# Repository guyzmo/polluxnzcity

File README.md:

Pollux'NZ City Project
======================

The pollux'NZ City project aims at creating a network of autonomous wireless network
of sensors that uploads the measures on any data silos on Internet.

This repository contains the source code of the first prototype of the project, that
has been deployed  in south of France, with the participation of INRIA Sofia Antipolis,
for a first test run.

Description
===========

The projects is made of two modules:
 * the 'autonomous measuring module', that is made of
   * an arduino with a zigbee radio module ;
   * a battery pack that powers the system ;
   * a solar panel that charges the battery ;
   * an i2c network of sensors.
 * the 'gateway module', that is made of
   * a beaglebone with a zigbee radio module

How it works ?
==============

First, after pluging it in, the user configures the gateway module for his sensor 
network and the interval time between two measures. Then he places the autonomous
sensor module to the best sunlight exposure so the autonomous measuring module can
keep the battery filled up.

The gateway will wait for the given interval time, and waken up the measuring module.
It will then order the measuring module to run the fan, so a free air sample is taken
into the box and run in sequence each sensor to get the measured value. Once all the
sensors have been interrogated, it will tell the measuring module to shut itself down.
Finally, all the measures are given to the enabled plugins that will push the data to
every configured data silo.

Project details
===============

Structure of the project
------------------------

 * Directories

<pre>
PolluxNZCity
    |-- PolluxConfig ............. Contains the configuration plugin (in python)
    |   |-- debian ............... Helper files for package generation
    |   |-- pollux ............... Python module
    |-- PolluxGateway ............ Main program that interfaces with the measuring modules
    |   |-- conf ................. Configuration files that are to be deployed in /etc
    |   |-- extensions ........... Python plugins for uploading data to data silos
    |   |-- include .............. Headers
    |   |-- src .................. Sources
    |   `-- tests ................ Tools that helps testing
    |-- PolluxWakeupduino ........ Main firmware code for the arduino in the measuring module
    |-- PolluxSensorBoard ........ Firmware code for the fan, temperature and noise board
    |-- PolluxSensorDust ......... Firmware code for the dust board
    |-- PolluxSensorSensoric ..... Firmware code for the electrochemical sensoric sensors board
    |-- PolluxSensorTemp ......... Firmware code for the external temperature sensor board
    `-- PolluxContribIpks ........ Helper scripts to build binary packages (for angstrom)
</pre>

 * Branches
   * inria_branch: contains the source code deployed for the INRIA test run
   * i2c_refactoring: non-tested base for a full refactoring of the i2c network

 * Other

In PolluxContribIpks, the package.sh script will run a build and generate the packages
– PolluxConfig and PolluxGateway – that are embedded on the beaglebone. That generator
is now deprecated, the recipes for generating those packages working and being accessible
for the angstrom build system.

Description of the main modules
-------------------------------

* _PolluxConfig_: this module is a web application based on the `bottle.py` module that
  exposes RESTful pathes to the web interface that exposes them using `bootstrap.js`.
  The most important parts are in the `pollux_config` module that contains all the exposed
  routes.
* _PolluxGateway_: this module is the main program that parses the configuration, runs 
  the radio, interrogates every sensor on the distant modules and sends the results
  through every datastore module.
* _PolluxWakeUpduino_: this firmware is the code executed by the embedded arduino that
  is only a gateway between XBee and the i2c network.

The _PolluxGateway_ module has documentation embedded you can generate using `doxygen`,
or by running `make doc` in the directory.

Build and Install
-----------------

* _PolluxConfig_

<pre>
 % cd PolluxConfig
 % python bootstrap.py
 % bin/buildout
 % bin/pollux_config_paster
</pre>

* _PolluxGateway_

first you will need to install the arm-gcc for crosscompilation, or run it directly
on a beaglebone, using native gcc.

<pre>
 % make
 % make doc
 % pollux\_gateway -h
</pre>

for a more verbose version of the software, you can run `make verbose`, that will
create a `pollux\_gateway\_verbose` executable.

Caveats
=======

* The I2C model has been mis-designed. 

We have implemented the i2c stack of the whole project following the way the i2c model
has been implemented in the Arduino and ATTiny wire library suggested ; so we followed
a function calling alike protocol.

But we rapidely found out that this kind of implementation is flawed for our use of 
i2c, as it is not flexible enough and not compatible with most of the i2c modules of
the market. So there's a unfinished implementation of the new i2c handling in the
`i2c_refactoring` branch. That has been not tested at all, and not all the sensors'
firmware has been switched to it.

* The _PolluxGateway_ modules deserves better verbosity

First, instead of compiling two different targets, it should have the common `-v`
switch that makes the executable output more messages. But the verbosity shall also
have levels, so the output is not flooded by the messages.

* The _PolluxGateway_ module shall not configure the MUX values for the xbee cape

We have implemented our first versions of the XBee Cape without the helper EEPROM
that helps the cape autoconfigure the MUX values of the beaglebone. With the new
version of the cape, all the code that configures the MUX settings shall be dropped.
This will finally makes the module work only in userland, and not need to start as
root and drop its privileges once the MUX settings are set.

* The _PolluxGateway_ module and _PolluxWakeUpduino_ firmware shall configure all the zigbee settings

We rely on the manual setting of the XBee modules, to match them up and to configure
their pin ports. That operation is cumbersome, does not work all the time, and needs
to use the X-CTU application under windows.

TODO
====

* finish the refactoring of the i2c stacks
* add more verbosity to the _PolluxGateway_ module
* remove the MUX configuration at _PolluxGateway_ start
* add configuration of the XBee radios in the _PolluxGateway_ module and
  _PolluxWakeUpduino_ firmware.

Copyright
=========

(c)2011-2013 Lucas Fernandez and Bernard Pratz, CKAB, hackable:Devices

 * http://polluxnzcity.org/
 * http://ckab.com/polluxnz-city/
 * http://hackable-devices.org/projects/project/polluxnzcity/

All our original work is licensed under the GNU GPL version 3
and all our schematics are under the Creative Commons v3.0 Attribution Share-Alike.

Here are the Libraries we use in our projects, and their respective copyrights notice

Arduino libraries:
 * Statistics by Rob Tillaart and Gil Ross, in the Public Domain 
 * usiTwiSlave, by Donald R. Blake, Jochen Toppe and Ben Galvin under GPL v2
 * circular buffer based on Akash Nath, in the Public Domain
 * Arduino, by the Arduino team, under the GPL v2

For the python web interface:
 * bottle.py under the MIT License
 * bootstrap.js under the Apache License v2.0.
 * deansi library by David Garcia Garzon, under the AGPLv3

All components symbols in the schematics are from Eagle's libraries, under Creative
Commons v3.0 Share-Alike.

License
=======

This program is free software: you can redistribute it and/or modify
it under the terms of the GNU General Public License as published by
the Free Software Foundation, either version 3 of the License, or
(at your option) any later version.

This program is distributed in the hope that it will be useful,
but WITHOUT ANY WARRANTY; without even the implied warranty of
MERCHANTABILITY or FITNESS FOR A PARTICULAR PURPOSE.  See the
GNU General Public License for more details.

You should have received a copy of the GNU General Public License
along with this program.  If not, see <http://www.gnu.org/licenses/>.

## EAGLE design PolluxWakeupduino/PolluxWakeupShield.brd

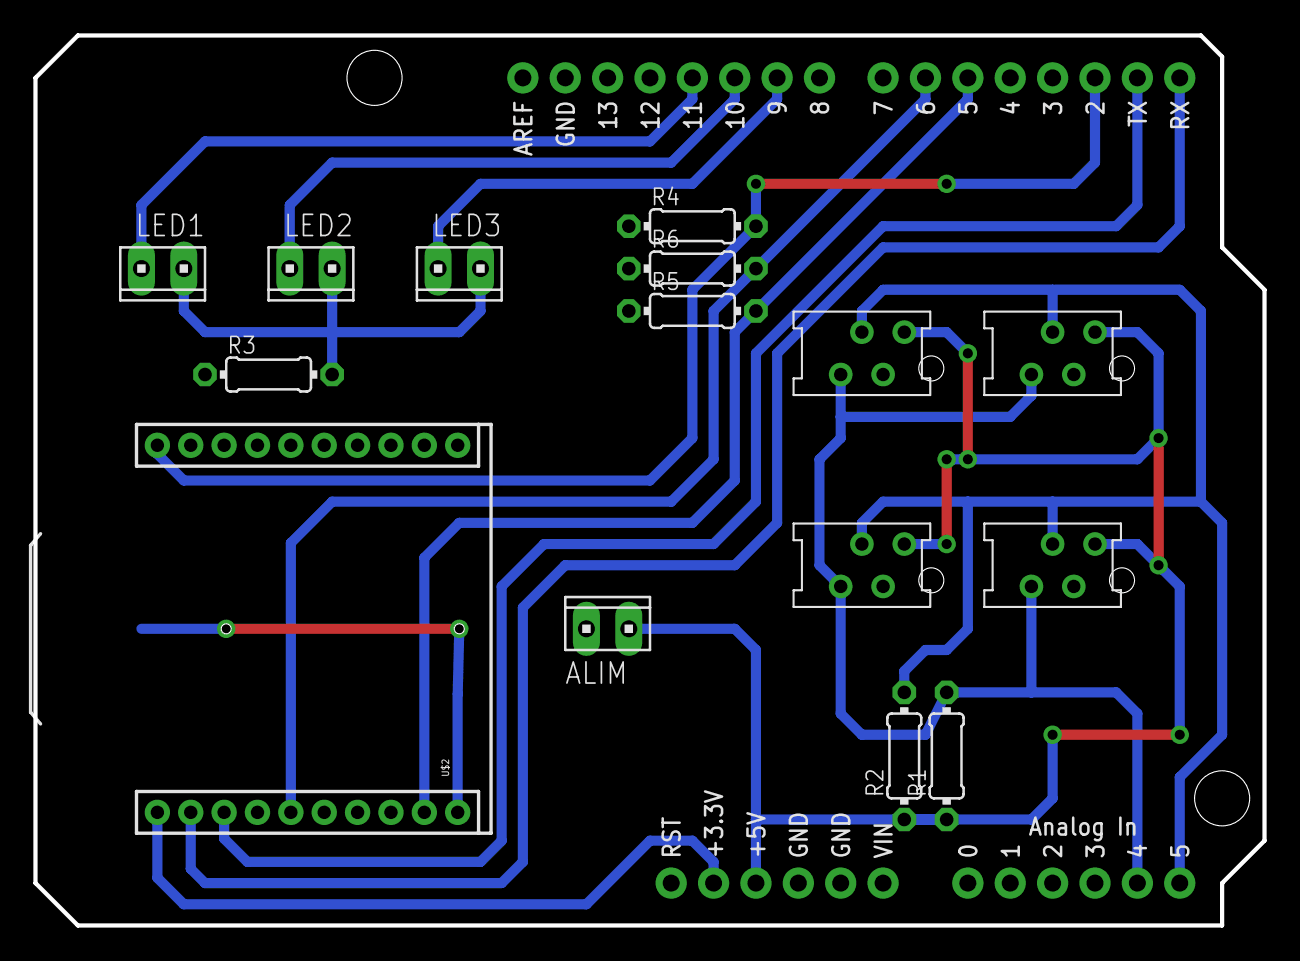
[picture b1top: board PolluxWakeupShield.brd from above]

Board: 2 copper layers, 73.7 x 53.3 mm, 16 parts (0 on the bottom side), 14 nets.

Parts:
ALIM: 10X02MTA
I2C-0, I2C-1, I2C-2, I2C-3: MMATCH-4-PTH; AMP-215079-4
LED1, LED2, LED3: 10X02MTA
R1, R2, R4, R5, R6: 10k; 0204/7
R3: 50; 0204/7
U1: ARDUINO_SHIELD; DUEMILANOVE_SHIELD
U$2: XBEE-1B2; XBEE-SILK

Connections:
3.3V: U1.3.3V, U$2.1
5V: ALIM.1, I2C-0.1, I2C-1.1, I2C-2.1, I2C-3.1, R1.1, R2.1, U1.5V
GND: ALIM.2, I2C-0.2, I2C-1.2, I2C-2.2, I2C-3.2, R3.1, R4.1, R5.1, R6.1, U1.GND@0, U1.GND@1, U1.GND@2, U$2.10
unnamed: LED1.2, LED2.2, LED3.2, R3.2
unnamed: LED3.1, U1.D9
unnamed: LED2.1, U1.D10
unnamed: LED1.1, U1.D11
RESET: R6.2, U1.D6, U$2.5
RX: U1.RX, U$2.2
SCL: I2C-0.3, I2C-1.3, I2C-2.3, I2C-3.3, R2.2, U1.A5
SDA: I2C-0.4, I2C-1.4, I2C-2.4, I2C-3.4, R1.2, U1.A4
SLEEP: R5.2, U1.D5, U$2.9
TX: U1.TX, U$2.3
WAKEUP: R4.2, U1.D2, U$2.20

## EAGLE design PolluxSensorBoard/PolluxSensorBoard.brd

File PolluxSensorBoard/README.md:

Sensor board for final fing pollux.

This sensor board include :
* temperature
* SPL
* Dust PM10

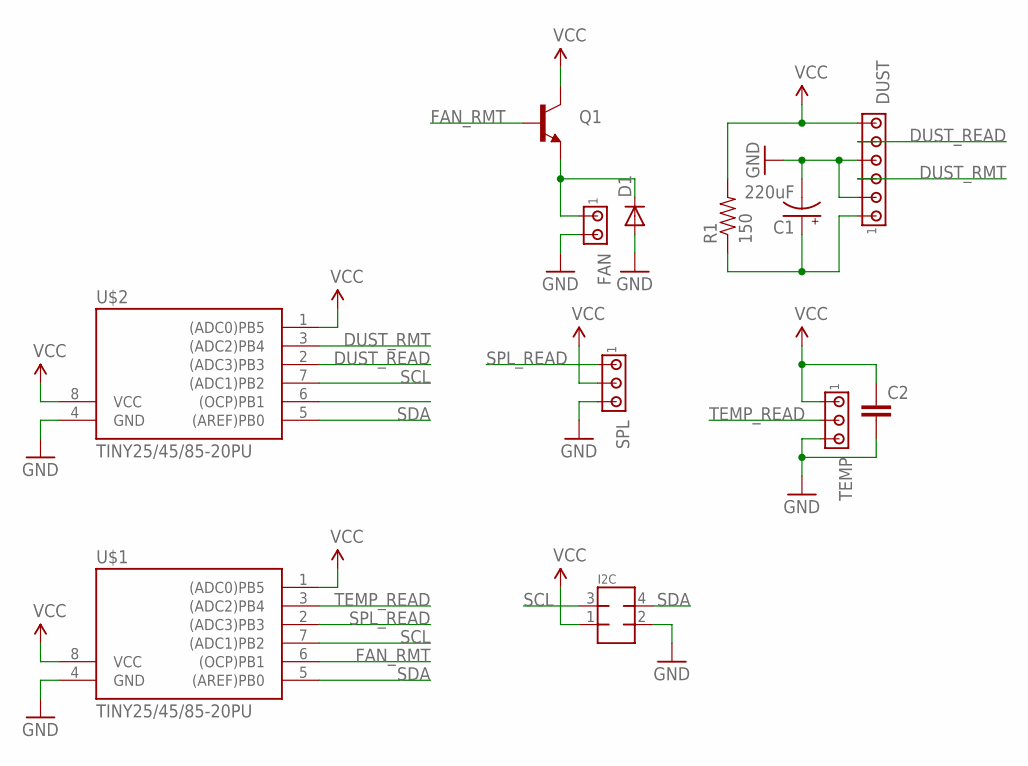
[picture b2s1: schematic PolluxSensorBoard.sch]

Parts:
C1: 220uF; CPOL-RADIAL-1000UF-25V
C2: CAPPTH1; CAP-PTH-5MM
D1: DIODEPTH; DIODE-1N4001
DUST: MTA06-100; 10X06MTA
FAN: MTA02-100; 10X02MTA
I2C: MMATCH-8-PTH; AMP-215079-8
Q1: TRANSISTOR_NPNTO-92-AMMO; TO-92-AMMO
R1: 150; AXIAL-0.4
SPL: MTA03-100; 10X03MTA
TEMP: MTA03-100; 10X03MTA
U$1, U$2: TINY25/45/85-20PU; DIL08

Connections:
DUST_READ: DUST.2 (5), U$2.2 ((ADC3)PB3)
DUST_RMT: DUST.4 (3), U$2.3 ((ADC2)PB4)
FAN_RMT: Q1.2 (B), U$1.6 ((OCP)PB1)
GND: C1.2 (-), C2.2, D1.A, DUST.3 (4), DUST.5 (2), FAN.2, I2C.2, SPL.3, TEMP.3, U$1.4 (GND), U$2.4 (GND)
unnamed: D1.C, FAN.1, Q1.1 (E)
unnamed: C1.1 (+), DUST.6 (1), R1.P$1 (1)
SCL: I2C.3, U$1.7 ((ADC1)PB2), U$2.7 ((ADC1)PB2)
SDA: I2C.4, U$1.5 ((AREF)PB0), U$2.5 ((AREF)PB0)
SPL_READ: SPL.1, U$1.2 ((ADC3)PB3)
TEMP_READ: TEMP.2, U$1.3 ((ADC2)PB4)
VCC: C2.1, DUST.1 (6), I2C.1, Q1.3 (C), R1.P$2 (2), SPL.2, TEMP.1, U$1.1 ((ADC0)PB5), U$1.8 (VCC), U$2.1 ((ADC0)PB5), U$2.8 (VCC)

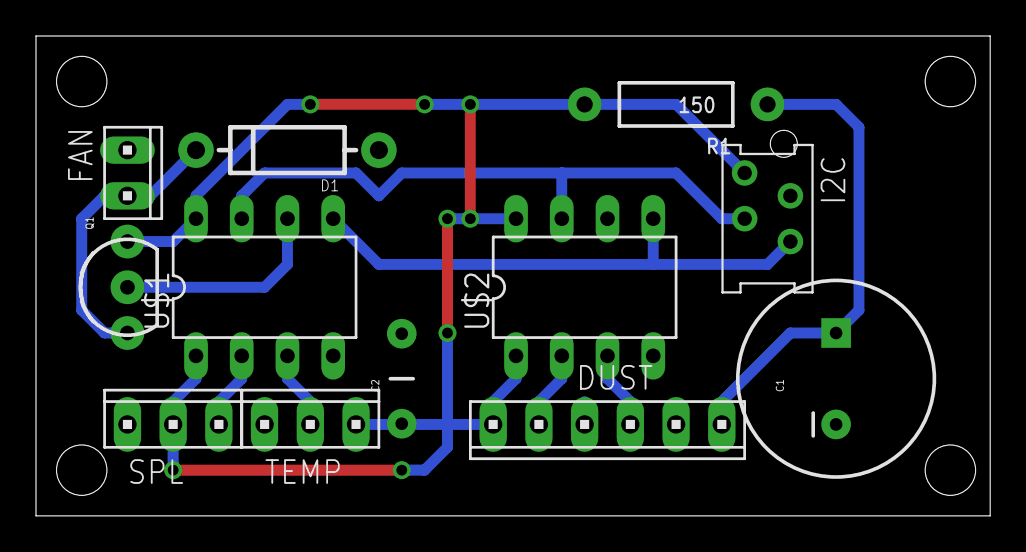
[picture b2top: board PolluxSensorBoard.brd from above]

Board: 2 copper layers, 53.0 x 26.7 mm, 12 parts (0 on the bottom side), 11 nets.

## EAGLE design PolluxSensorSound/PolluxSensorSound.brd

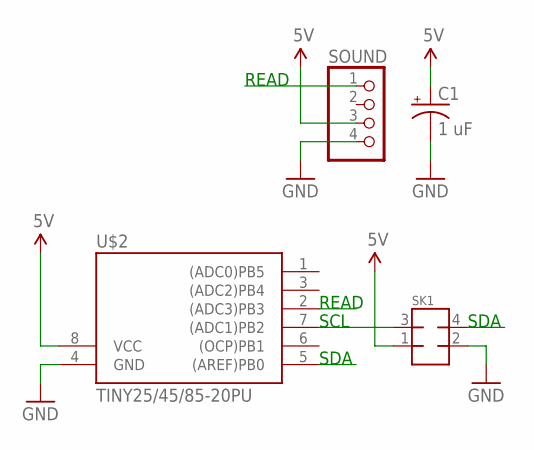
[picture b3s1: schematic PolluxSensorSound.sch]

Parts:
C1: 1 uF; CPOL-RADIAL-10UF-25V
SK1: MMATCH-8-PTH; AMP-215079-8
SOUND: PINHD-1X04_2.00; 1X04M
U$2: TINY25/45/85-20PU; DIL08

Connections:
5V: C1.1 (+), SK1.1, SOUND.3, U$2.8 (VCC)
GND: C1.2 (-), SK1.2, SOUND.4, U$2.4 (GND)
unnamed: SK1.3, U$2.7 ((ADC1)PB2)
READ: SOUND.1, U$2.2 ((ADC3)PB3)
SDA: SK1.4, U$2.5 ((AREF)PB0)

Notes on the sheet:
READ
SDA
SCL

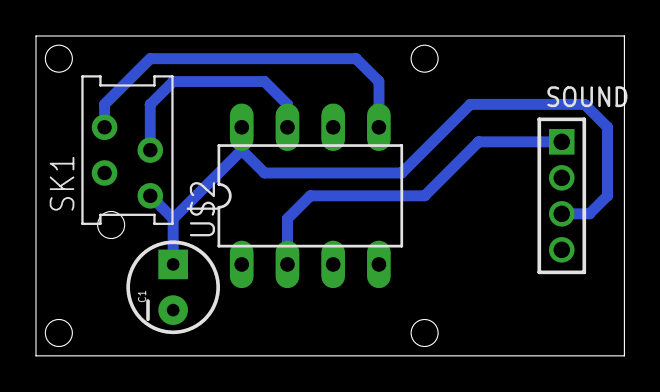
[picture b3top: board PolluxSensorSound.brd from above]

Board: 2 copper layers, 32.7 x 17.8 mm, 4 parts (0 on the bottom side), 5 nets.

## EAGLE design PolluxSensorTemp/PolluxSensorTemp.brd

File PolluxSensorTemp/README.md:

Board for dust detection for final fing pollux.

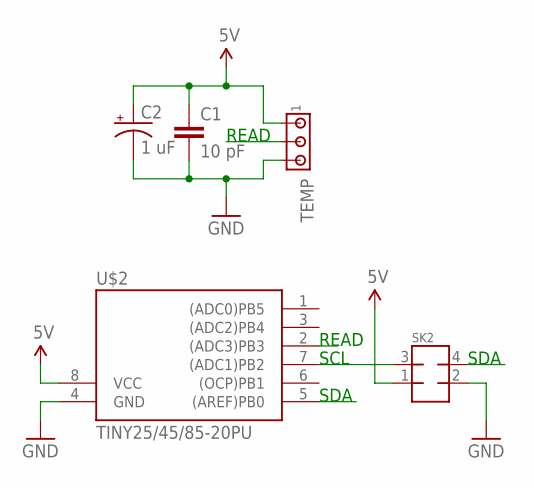
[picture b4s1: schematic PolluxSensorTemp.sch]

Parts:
C1: 10 pF; CAP-PTH-5MM
C2: 1 uF; CPOL-RADIAL-10UF-25V
SK2: MMATCH-8-PTH; AMP-215079-8
TEMP: MTA03-100; 10X03MTA
U$2: TINY25/45/85-20PU; DIL08

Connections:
5V: C1.1, C2.1 (+), SK2.1, TEMP.1, U$2.8 (VCC)
GND: C1.2, C2.2 (-), SK2.2, TEMP.3, U$2.4 (GND)
unnamed: SK2.3, U$2.7 ((ADC1)PB2)
READ: TEMP.2, U$2.2 ((ADC3)PB3)
SDA: SK2.4, U$2.5 ((AREF)PB0)

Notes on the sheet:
READ
SCL
SDA

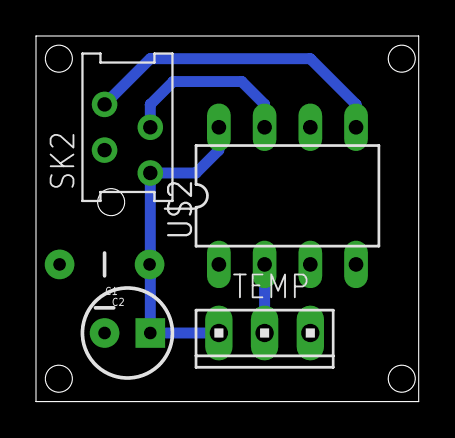
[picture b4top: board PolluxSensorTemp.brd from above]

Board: 2 copper layers, 21.3 x 20.3 mm, 5 parts (0 on the bottom side), 5 nets.

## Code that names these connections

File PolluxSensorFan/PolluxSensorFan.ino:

/*
             +-\/-+
   (RESET)  1|    |8  VCC (2.7-5.5V)
   NA ADC3  2|    |7  I2C   SCK -> Uno A5
       FAN  3|    |6  (PB1) NA
       GND  4|    |5  I2C   SDA -> Uno A4
             +----+ 
*/

#include "TinyWireS.h"      // ATTiny wire lib

#define I2C_SLAVE_ADDR 0x26 // I2C slave address

#define FAN_RMT        PB3  // Dust LED control on pin 3 (PB4)
#define DELAY_BASE     100  // basic delay 100 ms

byte byteRcvd ;
byte i;

void setup() {
  pinMode(FAN_RMT,OUTPUT);
  TinyWireS.begin(I2C_SLAVE_ADDR);
  i = 0;
  byteRcvd = 0;
}

void loop() {
  /*if (TinyWireS.available()) {           // if we get an I2C message
    byteRcvd = TinyWireS.receive();      // do nothing with the message
    digitalWrite(FAN_RMT, HIGH);         // set the LED on
    for(i=0;i<byteRcvd;i++)
      delay(DELAY_BASE);
    digitalWrite(FAN_RMT, LOW);          // set the LED on
  }*/
  if (TinyWireS.available()) {           // if we get an I2C message
    byteRcvd = TinyWireS.receive();      // do nothing with the message
    digitalWrite(FAN_RMT, HIGH);         // set the LED on
    delay(DELAY_BASE);
    digitalWrite(FAN_RMT, LOW);          // set the LED on
  }
}

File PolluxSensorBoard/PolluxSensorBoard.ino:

/**
 * Pollux'NZ City Project
 * Copyright (c) 2012 CKAB, hackable:Devices
 * Copyright (c) 2012 Bernard Pratz <guyzmo{at}hackable-devices{dot}org>
 * Copyright (c) 2012 Lucas Fernandez <kasey{at}hackable-devices{dot}org>
 *
 * Pollux'NZ City is free software: you can redistribute it and/or modify
 * it under the terms of the GNU General Public License as published by
 * the Free Software Foundation, either version 3 of the License, or
 * (at your option) any later version.
 *
 * Pollux'NZ City is distributed in the hope that it will be useful,
 * but WITHOUT ANY WARRANTY; without even the implied warranty of
 * MERCHANTABILITY or FITNESS FOR A PARTICULAR PURPOSE.  See the
 * GNU General Public License for more details.
 *
 * You should have received a copy of the GNU General Public License
 * along with this project. If not, see <http://www.gnu.org/licenses/>.

                  +-\/-+
        (RESET)  1|    |8  VCC (2.7-5.5V)
            SPL  2|    |7  I2C   SCK -> Uno A5
      Temp Read  3|    |6  Fan Remote
            GND  4|    |5  I2C   SDA -> Uno A4
                  +----+ 
*/
#define I2C_SLAVE_ADDR 0x27 // I2C slave address

//#define DESC "Temperature sensor"
#include <TinyWire.h>

#include "Statistic/Statistic.h"      // Arduino Statistic lib

#define TEMP_READ      2    // Temp  read on pin 3 (ADC2)
#define SPL_READ       3    // SPL   read on pin 2 (ADC3)
#define FAN_RMT        PB1  // Fan output on pin 6 (PB1)

#define DELAY_ADC       10  // time before re-read ADC 10 us

TinyWire Wire;


////////////////////////////////////////////////////////////////////////////////

// sensor  dbmeter
// 680  == 345 == 90dB
// 672  == 330 == 85dB
// 620  == 415 == 80dB
// 450? == 397 == 75dB
// 420? == 390 == 70dB
// 270  == 331 == 66dB
inline byte convert_to_dB(float val) {
    // 10.0 == 50dB
    if (val<10.0)        return 50; // <50dB
    // 15.0 == 55dB
    else if (val<15.0)   return 55; // <55dB
    // 30.0 == 60dB
    else if (val<30.0)   return 60; // <60dB
    // 70.0 == 65dB
    else if (val<70.0)   return 65; // <65dB
    // 140.0 == 70dB
    else if (val<140.0)  return 70; // <70dB
    // 230.0 == 75dB
    else if (val<230.0)  return 75; // <75dB
    // 250.0 == 80dB
    else if (val<255.0)  return 80; // <80dB
    // 255.0 == 85dB == 90 dB
    else if (val<255.0)  return 85; // <85dB
    else //if (val>=255.0)
        return 90; // >85dB
}

byte get_spl(Statistic* stat) {   
    byte result;

    for(uint8_t i=0;i<50;i++) {            // make 50 temperature sample
        stat->add(analogRead(SPL_READ));  // read and store temperature sensor output
        delayMicroseconds(DELAY_ADC);      // wait 10 us to stabilise ADC
    }

    result = (byte)convert_to_dB(stat->average());
    stat->clear();

    return result;
}

float get_temp(Statistic* stat) {
    float result;
    for(uint8_t i=0;i<50;i++) {            // make 50 temperature sample
        stat->add(analogRead(TEMP_READ));        // read and store temperature sensor output
        delayMicroseconds(DELAY_ADC);      // wait 10 us to stabilise ADC
    }

    result = ((stat->average()*0.0049)-0.5125)*100 ; // convert the result into a humain readable output

    if(result < 0) result = 0;             // avoid eratic datas
    stat->clear();                         // clear statistics to avoid leack and data stacking

    return result;
}

void run_fan() {
    digitalWrite(PB1,HIGH);
    for (int i=0;i<10;++i)
        delay(10000);
    digitalWrite(PB1,LOW);
}

////////////////////////////////////////////////////////////////////////////////
uint8_t i=0;

void sensor_meas() {
    Statistic stat;
    float res_f = 0;
    uint8_t res_b = 0;

    uint8_t* float_ptr;

    switch (i++) {
        case 0:
            run_fan();
            Wire.set_type(I2C_INT);
            Wire.write((uint8_t)0xFF); // msb
            Wire.write((uint8_t)0xFF); // lsb
            break;

        case 1:
            res_b = get_spl(&stat);
            Wire.set_type(I2C_INT);
            Wire.write((uint8_t)res_b); // msb
            Wire.write((uint8_t)0x0);   // lsb
            break;
            
        case 2:
            res_f = get_temp(&stat);
            float_ptr = (uint8_t*)&res_f;
            Wire.set_type(I2C_FLT);
            Wire.write(*(float_ptr)); // send 1st byte of float
            Wire.write(*(float_ptr+1)); // send 2nd byte of float
            Wire.write(*(float_ptr+2)); // send 3rd byte of float
            Wire.write(*(float_ptr+3)); // send 4th byte of float
            break;
    }
    if (i == 3) i = 0;
}

void setup() {
    pinMode(PB1,OUTPUT);
    pinMode(TEMP_READ,INPUT);
    pinMode(SPL_READ,INPUT);

    Wire.begin(I2C_SLAVE_ADDR); // slave address
    Wire.set_request_callback(&sensor_meas);
}

void loop() {
 /* nop */
}

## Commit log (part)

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2011-12-02 [FIX #424] code for temperature sensor
2011-12-03 [ENH #423] Added code for NO2 sensor. Need more validation.
2011-12-03 [ENH #422] added dust sensor code
2011-12-03 [ENH #421] added code for CO measurement.
2012-02-14 removing sensor test files, already sent to the branch sensor-test
2012-02-14 [ENH #625] added gateway and sensor initial codes
2012-02-14 [ENH #625] added Makefiles
2012-02-14 [ENH #625] modified sketches
2012-02-15 [ENH #625] added XbeeCommunicator class skeleton to gateway
2012-02-22 change file tree and add dust slave and master
2012-02-22 add Sound and temperature codes
2012-02-22 adapt captor template to SPL
2012-02-22 remove custom makefile
2012-02-22 initial pop schematic and board for dust sensor
2012-02-22 add sensors schematics and brd
2012-02-22 [ENH #425] added noise sensor code
2012-02-22 add dust sensor schematics and board
2012-02-22 add Temp sensor board and schematics
2012-02-22 add SPL sensor board and schematics
2012-02-22 xbee api communicator library added ; makefile updated
2012-02-23 improve sensor board
2012-02-24 moved .pde to .ino in pollux wud
2012-03-01 [ENH #625] adeed monitor option to makefile
2012-03-01 [ENH #625] added xbee communicator library ; updated gateway sketch
2012-03-01 [ENH #625 added monitor to makefile]
2012-03-01 [ENH #625] updated PolluxWUD sketch
2012-03-01 [ENH #625] reverted to XBee original library
2012-03-02 removed Makefile
2012-03-02 added pollux gateway base code and init uart script
2012-03-02 added python blinky GPIO PoC
2012-03-03 moved blinky into test directory
2012-03-03 updated comments in init uart2
2012-03-03 [ENH #625] moved xbee lib into new file name
2012-03-03 [ENH #625] updated several test code into library
2012-03-03 [ENH #625] minor fix
2012-03-03 [ENH #625] updated pollux WUD code to communicate through xbee
2012-03-04 minor change
2012-03-04 [ENH #625] added beaglebone led features and enabled them
2012-03-04 [ENH #625] housekeeping, disabled leds on ^C
2012-03-04 [ENH #625] refactored libraries to separate .h/.C
2012-03-04 [ENH #625] updated Makefile ; refactored code in different directories
2012-03-04 [ENH #625] refactored code in different directories
2012-03-04 [ENH #625] housekeeping
2012-03-04 [ENH #625] minor updates
2012-03-04 added GPLv2 License and copyrights in all sources
2012-03-04 [ENH #625] enabling/disabling UART2 from source code
2012-03-05 added placeholder for i2c code
2012-03-05 improve sound sensor
2012-03-07 Add new board schematic and brd
2012-03-07 Add code for new sensor board
2012-03-08 updated to last Makefile gen
2012-03-08 working i2c version of temperature
2012-03-08 updated WUD code
2012-03-09 added citypulse code and placeholder
2012-03-09 modified makefile for attiny
2012-03-09 updated tinywire library and polluxsensortemp code
2012-03-09 minor modification
2012-03-11 add Wakeupshield with I2C and XBee connector. Recently added wakeup from xbee and sleep mode from arduino
2012-03-13 [ENH #625] updated led report stuff
2012-03-13 removed PB4 led debug
2012-03-13 added new shield LED support
2012-03-13 added reset in makefile
2012-03-13 removed all not directly useful code -- saved in sensor-proto branch
2012-03-13 [ENH #623] added tinywireslave's code to pollux sensorboard
2012-03-13 [ENH #623] removed old pollux temperature code
2012-03-13 [ENH #623] moved shield schematics to wakeupduino folder
2012-03-13 dd last schematics with xbee improvement
2012-03-22 [ENH #625] working code receiving zigbee data
2012-03-22 [ENH #625] working code sending to zb router
2012-03-23 [ENH #625] updated Pollux WUD code as a i2c<->zigbee bridge ; working code
2012-03-23 [ENH #625] updated pollux libraries for WUD for a bit of genericity
2012-03-23 removed stale file
2012-03-23 [ENH #623] updated TinyWire library
2012-03-23 removed stale object file
2012-03-23 [ENH #623] updated last sensor code for SensorBoard ; working code
2012-03-23 [ENH #623] removed old tinywire lib
2012-03-23 [ENH #623] added updated tinywire lib
2012-03-23 [ENH #623] added readme
2012-03-23 [ENH #623] updated makefile
2012-03-23 minor copyright update
2012-03-23 [ENH #623] added dust sensor code ; not working (gives 0.0 value...)
2012-03-23 [ENH #623] updated i2c communication so it halts when alone ; corrected hardcoded addresses in code
2012-03-23 [ENH #623] added halt command
2012-03-23 [ENH #623][ENH #625] added i2c<->zigbee poll loop for multiple sensor checking
2012-03-23 removed verbosity from gateway
2012-03-23 [ENH #626][ENH #625][ENH #624] added mockup of observer pattern for multiple sensors support ; added static sensors definition ; added JSON data build
2012-03-23 [ENH #626] added sha1 hash code ; added transmission to citypulse code
2012-03-23 [ENH #626] added transmission to citypulse code in pollux gateway
2012-03-24 added json configuration file parsing test file and command line parsing
2012-03-25 added updated sensors test file
2012-03-25 added measure iteration and hashmap creation
2012-03-25 added node address array to long converter method ; removed unit from action
2012-03-25 added basis for configuration utility
2012-03-25 added readme for gateway
2012-03-26 added pollux config python code and template file
2012-03-26 updated error management
2012-03-26 added jquery
2012-03-27 [ENH #625] added sleep mode support and wakeup by int
2012-03-28 [ENH #626] removing quotes from values of measures
2012-03-28 Add sensoric AVR code
2012-03-28 add mako/templates/full website frontend :)
2012-03-28 enhance backend sensor + advenced
2012-03-28 add active/unactive datastorage
2012-03-28 all feature ok, last commit before beta
2012-03-28 add some improvements and all checks ok
2012-03-28 added configuration files
2012-03-29 added CSV viewing support
2012-03-31 [ENH #623] added halt commit feature
2012-03-31 updated pollux code so it works in master.
2012-03-31 updated code with sleep time support from config ; with working sensors reading and pushing
2012-04-13 added wakeup support at launch
2012-04-13 added configuration support on citypulse ; extracted json creation in citypulse module ; fixed sha1 buffer bug ; extracted types to pollux_toolbox
2012-04-13 added local csv module
2012-04-13 exported all json creation to citypulse module ; added config support in citypulse module
2012-04-13 added uint64_t support to xbee communicator
2012-04-13 extracted local_csv and json/csv creation ; put many outputs to debug mode only ; added trailing / support for path
2012-04-13 updated main code so order of sensors is respected
2012-04-13 removed last constant references to module's address ; improved output
2012-04-14 added namespaces ; fixed makefile
2012-04-14 minor update
2012-04-14 added dynamic library support for datastores addon feature
2012-04-14 minor improvements on outputs and corrected name mangling for C callback
2012-04-14 added dynamic library support for datastores addon feature ; failure on execution
2012-04-16 added bitbake file to be tested
2012-04-17 updated makefile
2012-04-17 added service file
2012-04-17 fixed extension loading module
2012-04-17 updated configurator so it takes plugin path separately
2012-04-17 updated makefile to install extensions where it belongs
2012-04-17 updated pathes in service
2012-04-17 added base support for calibration
2012-04-17 updated pollux config in master
2012-04-17 added uninstall support in polluxconfig
2012-04-17 added configuration validation script
2012-04-19 updated homepage
2012-04-20 added datastore activation support ; improved sensors support
2012-04-20 changed TinyWire model
2012-04-20 fixed sensors code to support generation from sensors_list.json
2012-04-21 added comments, moved signal handling
2012-04-21 added comments ; refactored to extract prober/calibrator from configuration ; added pollux_calibrator code ; extracted signal handling from pollux_xbee
2012-04-21 updated sensors_list
2012-04-21 updated makefile install
2012-04-21 solved compilation issues ; updated support for unprivileged execution
2012-04-25 updated code to support cross compilation and packet generation
2012-04-25 added meta-package generation
2012-04-25 added package generation to pollux config
2012-04-25 added debian info files
2012-04-25 improved lighttpd service
2012-04-25 made lighttpd configuration works
2012-04-26 added packaging tools and feed creation
2012-04-27 updated feed generation bugs
2012-04-27 updated sensors' list source
2012-04-27 added beta branding
2012-04-27 updated generation of pollux-full
2012-04-27 corrected pollux_gateway service ; added better version support ; added crontab scripts to pollux-full ; improved update_feed
2012-04-27 removed empty data file for pollux-full
2012-04-27 added pathes to documentation generation
2012-04-28 added pollux_gateway_verbose
2012-04-28 updated pollux gateway to output correctly local output ; fixed bug in parsing values_list ; added verbose target
2012-04-28 fixed data path
2012-04-28 updated debian stuff, depndencies, file creation and ownership...
2012-04-28 updated lighttpd-systemd for it to be launched at startup and install
2012-04-28 updated Makefile of gateway
2012-05-03 added support for python extension
2012-05-03 added python plugin support
2012-05-03 updated python support
2012-05-04 updgraded Makefile for PolluxGateway
2012-05-04 changed extensions from C to Python
2012-05-04 added python module support
2012-05-04 added support for '-s' option to avoid the fork
2012-05-04 updated .gitignore
2012-05-04 updated makefiles
2012-05-04 updated version
2012-05-05 refactored module's name pollux_xbee to pollux_observer
2012-05-05 added verbose target
2012-05-05 decreased timeout in citypulse's module
2012-05-05 made LOW/HIGH commands globals consts
2012-05-05 removed stale code
2012-05-05 updated version string
2012-05-05 fixed minor regression
2012-05-05 added verbosity flags to compilation ; corrected warnings' causes
2012-05-05 added datas to main template
2012-05-05 added support for python modules
2012-05-05 improved data viewing
2012-05-05 updated pollux config to 0.2.0
2012-05-05 updated pollux task to 0.2
2012-05-05 updated Makefile with better xcompile support
2012-05-05 updated postinst for upgrades
2012-05-05 minor fix
2012-05-05 updated text on module upload
2012-05-05 fixed minor bug
2012-05-09 minor updates to pollux WUD
2012-05-09 updated Makefil ; fixed bugs in python extensions
2012-05-09 fixed bug: bringing WUD off when timeout
2012-05-09 fixed format warning
2012-05-09 added ugly fix to be sure WUD wakes up (on/off/on at each wakeup...)
2012-05-22 added upload module support
2012-05-22 commented out disabled buttons
2012-05-22 improve OSM functions
2012-05-31 added support for status of services in case of no logs
2012-05-31 added name checking for module upload
2012-05-31 added LICENSE file placeholder
2012-08-24 [ENH] updated buildout/setup
2012-08-24 [ENH] removed mako and bottle from source tree
2012-08-24 [ENH] added plugin remove feature
2012-08-28 [ENH] updated Makefile for bitbake integration
2012-08-28 [ENH] added LICENSE to PolluxConfig
2012-08-29 [ENH] updated setup.py to deploy etc files too
2012-08-29 [FIX] typos in setup.py
2012-08-29 [ENH] moved config files from PolluxConfig to PolluxGateway
2012-08-29 [ENH] updated Makefile to match new .service path for pollux_gateway
2012-08-30 [ENH] added service file for avahi
2012-09-03 add new sensor temp
2012-09-06 [ENH] updated configurator
2012-09-06 [ENH] removed test points from gateway makefile
2012-09-06 [ENH] added pachube plugin to repository
2012-09-06 add function to convert res in celcius temp
2012-09-06 Revert "updated default values to sensor dust"
    This reverts commit 4c4130744d3128e336709e3b6a73def85ad82c9f.
2012-09-06 [FIX] reverted 4c413074,2713b195,1ad7e67 on PolluxSensorDust to get back to original TinyWire model
2012-09-06 [ENH] updated UPLOAD_RATE of all attiny makefiles to 19200
2012-09-06 [FIX] refactored pollux sensor temp to original tinywire model
2012-09-06 [ENH] added new temperature calculation function (not tested)
2013-01-23 [FIX] corrected path to attiny files in Pollux Temperature Sensor
2013-01-23 [FIX] improved temperature correction in SensorBoard
2013-01-23 [ENH] removed empty view decorator
2013-01-23 [ENH] added README file
2013-02-19 [ENH] updated licensing and copyright notices

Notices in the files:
parts and their libraries:
SparkFun: Licensing: CC v3.0 Share-Alike You are welcome to use this library for commercial purposes.
